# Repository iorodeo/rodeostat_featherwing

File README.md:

# IO Rodeo Potentiostat Feather Wing

Hardware design for IO Rodeo's Rodeostat Featherwing.

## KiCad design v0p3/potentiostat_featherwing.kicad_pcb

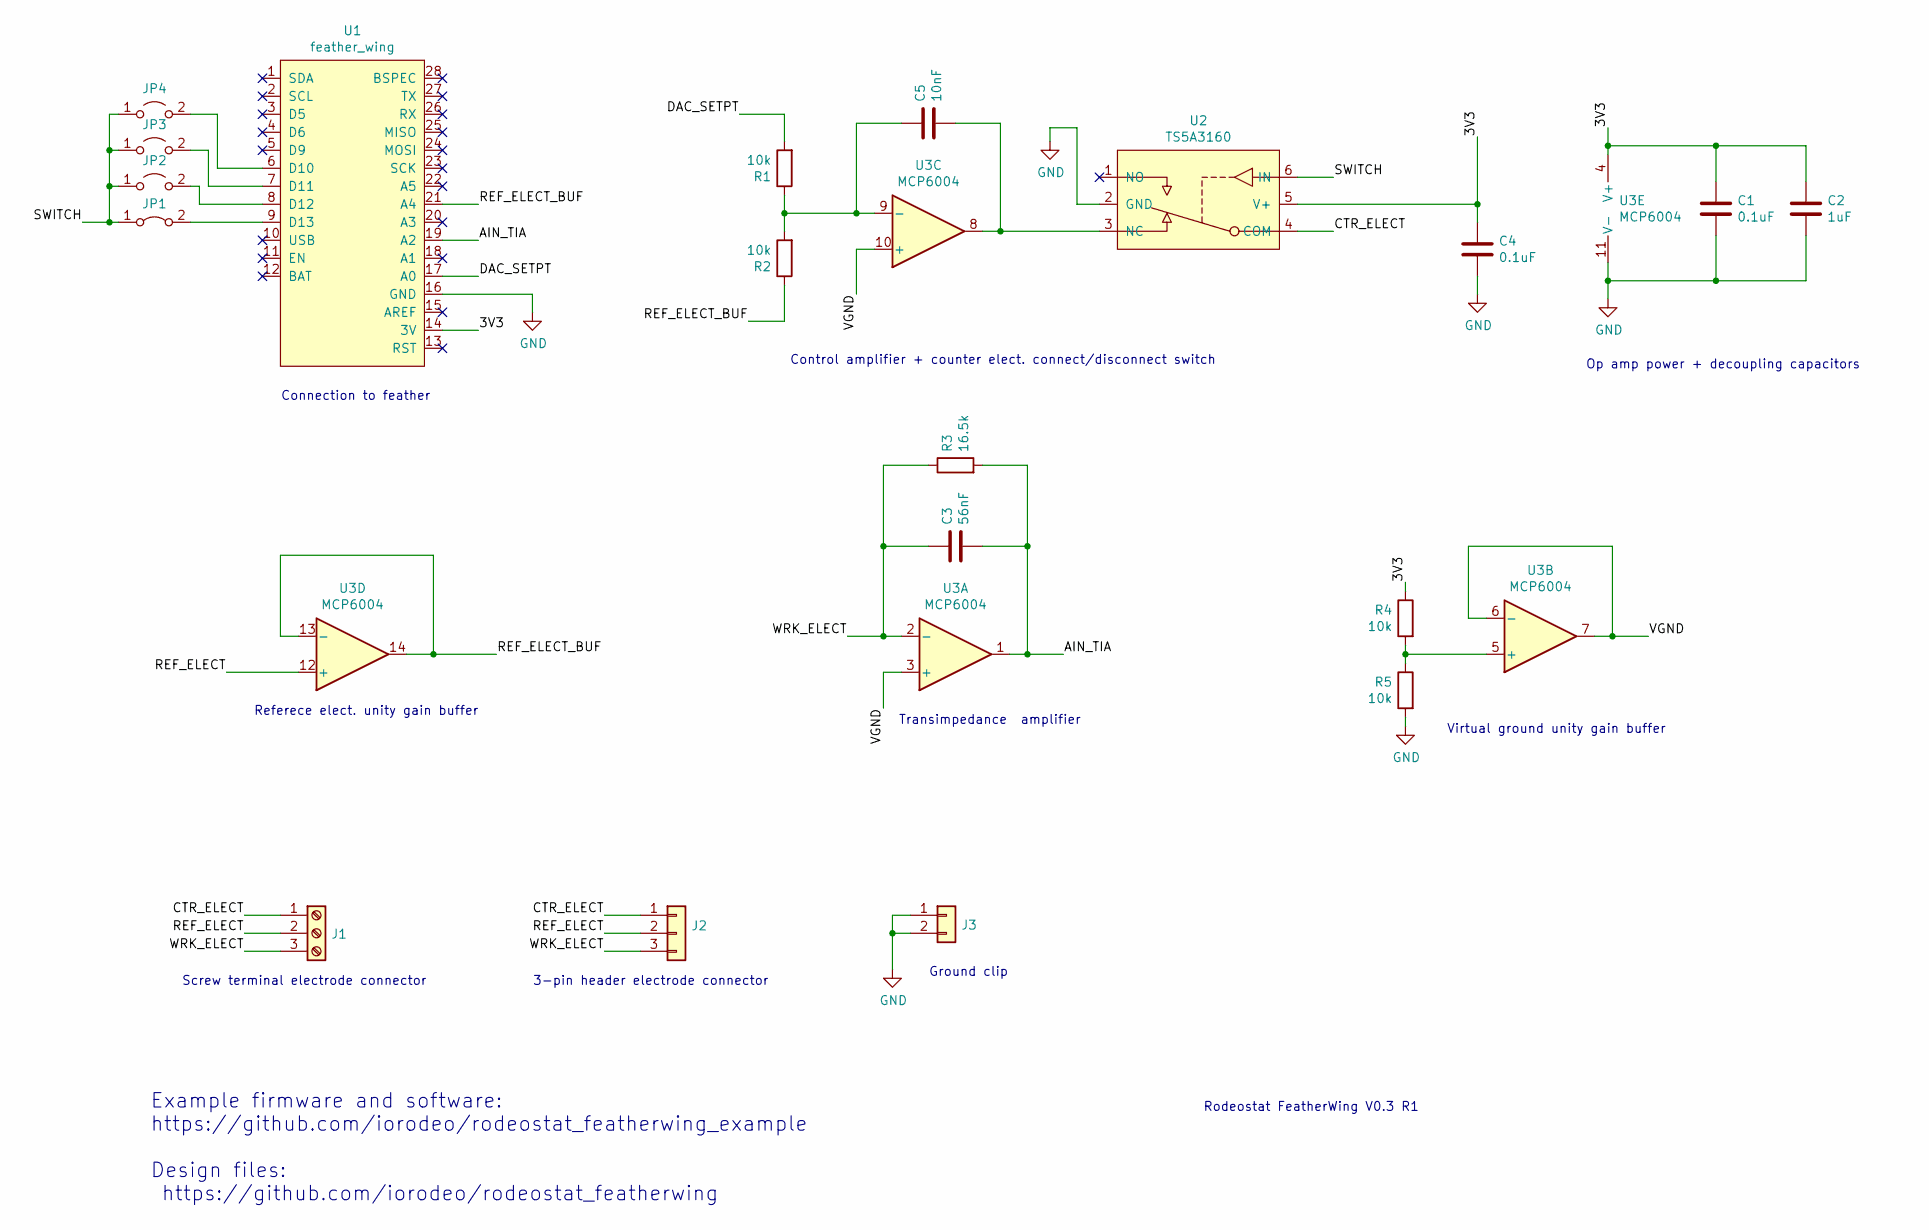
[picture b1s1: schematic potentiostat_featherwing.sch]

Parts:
C1, C4: 0.1uF; C_0603_1608Metric
C2: 1uF; C_0603_1608Metric
C3: 56nF; C_0603_1608Metric
C5: 10nF; C_0603_1608Metric
J1: Screw_Terminal_01x03; CONNBLOCK3
J2: Conn_01x03; PinHeader_1x03_P2.54mm_Vertical
J3: Conn_01x02; PinHeader_1x02_P2.54mm_Vertical
JP1: Jumper_2_Bridged; SolderJumper-2_P1.3mm_Bridged_Pad1.0x1.5mm
JP2, JP3, JP4: Jumper_2_Open; SolderJumper-2_P1.3mm_Open_TrianglePad1.0x1.5mm
R1, R2, R4, R5: 10k; R_0603_1608Metric
R3: 16.5k; R_0603_1608Metric_Pad0.98x0.95mm_HandSolder
U1: feather_wing
U2: TS5A3160; SOT-23-6
U3: MCP6004; SOIC-14_3.9x8.7mm_P1.27mm

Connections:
/3V3: C1.1, C2.1, C4.1, R4.1, U1.14 (3V), U2.5 (V+), U3.4 (V+)
/AIN_TIA: C3.2, R3.2, U1.19 (A2), U3.1
/CTR_ELECT: J1.1, J2.1, U2.4 (COM)
/DAC_SETPT: R1.2, U1.17 (A0)
/REF_ELECT: J1.2, J2.2, U3.12 (+)
/REF_ELECT_BUF: R2.1, U1.21 (A4), U3.13 (-), U3.14
/SWITCH: JP1.1 (A), JP2.1 (A), JP3.1 (A), JP4.1 (A), U2.6 (IN)
/VGND: U3.3 (+), U3.6 (-), U3.7, U3.10 (+)
/WRK_ELECT: C3.1, J1.3, J2.3, R3.1, U3.2 (-)
GND: C1.2, C2.2, C4.2, J3.1, J3.2, R5.2, U1.16 (GND), U2.2 (GND), U3.11 (V-)
unnamed: C5.1, U2.3 (NC), U3.8
unnamed: C5.2, R1.1, R2.2, U3.9 (-)
unnamed: JP1.2 (B), U1.9 (D13)
unnamed: JP2.2 (B), U1.8 (D12)
unnamed: JP3.2 (B), U1.7 (D11)
unnamed: JP4.2 (B), U1.6 (D10)
unnamed: R4.2, R5.1, U3.5 (+)

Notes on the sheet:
Screw terminal electrode connector
3-pin header electrode connector
Referece elect. unity gain buffer
Connection to feather
Control amplifier + counter elect. connect/disconnect switch
Op amp power + decoupling capacitors
Virtual ground unity gain buffer
Transimpedance amplifier
Ground clip
Rodeostat FeatherWing V0.3 R1
Example firmware and software: https://github.com/iorodeo/rodeostat_featherwing_example Design files: https://github.com/iorodeo/rodeostat_featherwing

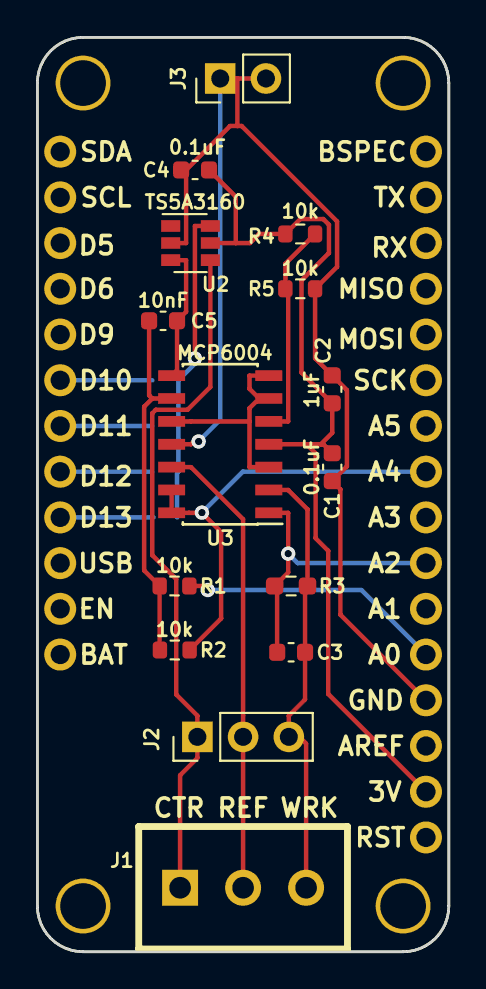
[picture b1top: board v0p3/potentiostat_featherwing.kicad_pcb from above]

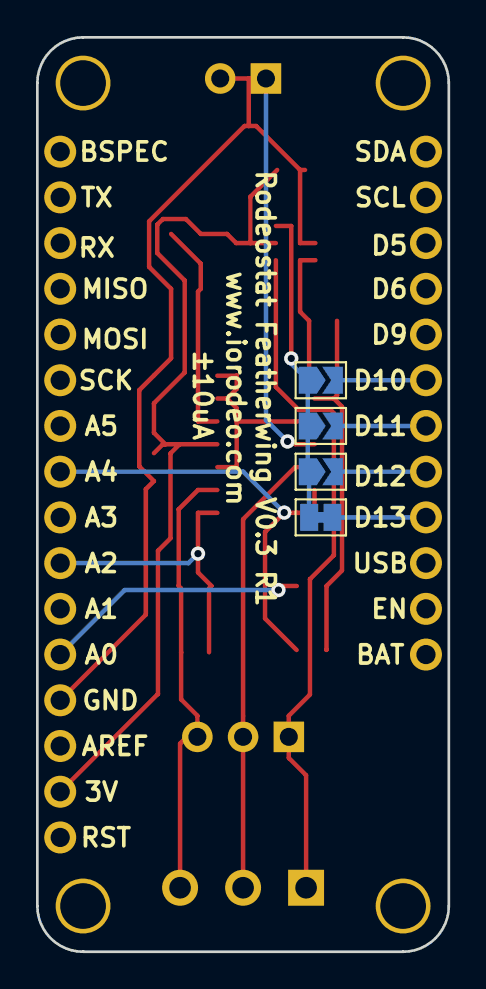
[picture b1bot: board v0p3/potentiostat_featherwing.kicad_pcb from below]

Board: 2 copper layers, 22.9 x 50.8 mm, 20 parts (4 on the bottom side), 17 nets.

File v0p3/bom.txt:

Digikey
=======

Ref           Description                   Package       Vendor      Part Number           Qty       
-----------------------------------------------------------------------------------------------
C1,C4         capacitor, 0.1uF, ceramic     0603          Digikey     399-1099-1-ND          2  
C2            capacitor, 1.0uF, ceramic     0603          Digikey     399-7847-1-ND          1  
C3            capacitor, 56nF,  ceramic     0603          Digikey     478-1236-1-ND          1  
C5            capacitor, 10nF,  ceramic     0603          Digikey     311-1085-1-ND          1  
J1            screw term, 3-pos             NA            Digikey     ED2636-ND              1  
J2            1x3 male header               NA            Digikey     S1011EC-40-ND          1  
J3            jumper wire                   NA            Digikey     923345-01-ND           1  
R1,R2,R4,R5   resistor, 10k                 0603          Digikey     P10KDBCT-ND            4  
R3            resistor, 16.5k               0603          Digikey     P16.5KDBCT-ND          1  
U2            TS5A3160 SPDT Analog Switch   SOT-23-6L     Digikey  	  296-21189-1-ND         1  
U3            Quad op amp MCP6004           14-SOIC       Digikey     MCP6004T-I/SLCT-ND     1  



JCLPCB
======

Ref           Description                   Package                  Vendor    Type     Part Number      Qty       
------------------------------------------------------------------------------------------------------------
C1,C4         capacitor, 0.1uF, ceramic     0603                     JLCPCB      B       C14663	          2  
C2            capacitor, 1.0uF, ceramic     0603                     JLCPCB      B       C15849           1  
C3            capacitor, 68nF,  ceramic     0603                     JLCPCB      B       C31658           1  
C5            capacitor, 10nF,  ceramic     0603                     JLCPCB      B       C57112	          1  
R1,R2,R4,R5   resistor, 10k                 0603                     JLCPCB      E       C190321          4    
U2            TS5A3160 SPDT Analog Switch   SOT-23-6L                JLCPCB      E       C185770	      1  
U3            Quad op amp MCP6004           SOIC-14_3.9x8.7x1.27P    JLCPCB      E       C7378	          1  

R3 skip


Old Parts
=========

U2            ADG702 SPST-NC switch,        SOT-23-6      Digikey     ADG702BRTZ-REEL7CT-ND  1  
U2            ADG702 SPST-NC switch,        SOT-23-6L                JLCPCB      E       C133478          1

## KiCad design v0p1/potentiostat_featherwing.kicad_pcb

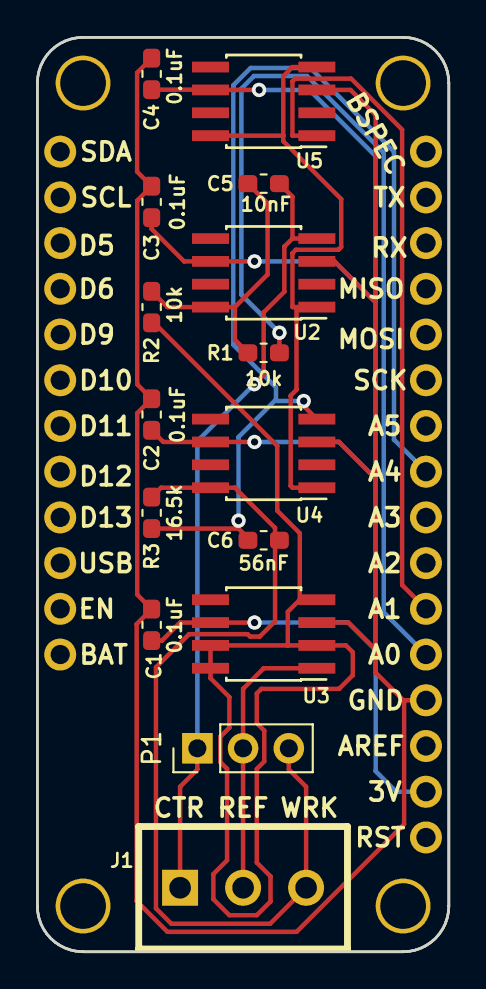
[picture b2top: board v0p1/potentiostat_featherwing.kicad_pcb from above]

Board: 2 copper layers, 22.9 x 50.8 mm, 16 parts (0 on the bottom side), 11 nets.

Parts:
C1, C2, C3, C4: 0.1uF; C_0603_1608Metric_Pad1.05x0.95mm_HandSolder
C5: 10nF; C_0603_1608Metric_Pad1.05x0.95mm_HandSolder
C6: 56nF; C_0603_1608Metric_Pad1.05x0.95mm_HandSolder
J1: Screw_Terminal_01x03; CONNBLOCK3
P1: pin_array_3x1; PinHeader_1x03_P2.54mm_Vertical
R1, R2: 10k; R_0603_1608Metric_Pad1.05x0.95mm_HandSolder
R3: 16.5k; R_0603_1608Metric_Pad1.05x0.95mm_HandSolder
U1: feather_wing
U2, U3, U4, U5: LMP7721; SOIC-8_3.9x4.9mm_P1.27mm_HandSolder

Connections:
/3V3: C1.1, C2.1, C3.1, C4.1, U1.14, U2.6, U3.6, U4.6, U5.6
/AIN_TIA: C6.2, R3.2, U1.21, U4.4
/CTR_ELECT: C5.1, J1.1, P1.1, U2.4
/DAC_SETPT: R1.2, U1.17
/DAC_VGND: U1.18, U5.1
/REF_ELECT: J1.2, P1.2, U3.1
/REF_ELECT_BUF: R2.2, U3.2, U3.4, U3.7, U3.8
/VGND: U2.1, U4.1, U5.4, U5.8
/WRK_ELECT: C6.1, J1.3, P1.3, R3.1, U4.8
GND: C1.2, C2.2, C3.2, C4.2, U1.16, U2.3, U3.3, U4.3, U5.3
unnamed: C5.2, R1.1, R2.1, U2.8

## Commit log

2019-08-22 Project creation.
2019-08-22 Fixed issue with readme.
2019-08-22 Another change to readme.
2019-08-22 Yet another change to readme.
2019-08-22 Added license.
2019-09-12 Modified design so that ref elect (buffered) can be measured by analog input.
2020-02-03 Added new v0.2 version of the featherwing design.
2020-02-06 Created version 0.2 of the design. Changed op amps. Added switch. Added ground test point.
2020-02-13 Fixed issue with v0p2 BOM.
2020-03-31 Added images of v0.2 design.
2020-03-31 Added 3d rendering.
2020-03-31 Fixed readme.
2020-06-14 Minor modifications for schematic - no substantive changes. Remade gerber files for v0p2_r2.
2020-12-13 Added v0p3 of design. Modified for turnkey assembly.
2020-12-13 Fixed component orientations is CPL file.
2020-12-28 Modified readme.
2021-01-12 Remade pdf of schematic.
2021-01-12 Remade pdf of schematic add links to repositories.
2021-10-03 Added gerbers, BOM and CPL for the four different ranges.
2021-10-29 Modified schematics so resistor values for different current ranges are shown.
2023-01-27 Added alternative BOM for 100uA design.
2023-05-29 Added alternate BOM for rodeostat featherwing.
